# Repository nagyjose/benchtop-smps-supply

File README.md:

# Benchtop Switched-Mode Power Supply (`benchtop-smps-supply`)

> Multi-rail laboratory benchtop power supply providing fixed +12V DC, +5V DC, and dual bipolar adjustable outputs (LM317 / LM337), powered by an isolated offline flyback converter with the Power Integrations TNY267PN.

**Project Status:** `Completed / Hardware Design Ready` | **EDA Tool:** `Autodesk Eagle 9.6.2` | **Category:** `Power Electronics / Hardware`

---

## 1. Overview and Purpose

The **`benchtop-smps-supply`** project is an offline AC/DC power supply engineered for benchtop laboratory instrumentation and electronics prototyping. Powered directly from wide-range AC mains (85–265 V AC, 50/60 Hz), it provides four distinct regulated DC output rails to drive analog circuitry, operational amplifiers, digital microcontrollers, and experimental breadboards:

1. **Fixed +12 V DC Rail:** Regulated via STMicroelectronics L7812 for relay drivers, fans, sensors, and analog stages.
2. **Fixed +5 V DC Rail:** Regulated via STMicroelectronics L7805 for digital logic, microcontrollers (Arduino, STM32), and display modules.
3. **Adjustable Positive Rail (`V+`):** Adjustable from **+1.25 V to ~+15–18 V DC** via Texas Instruments / ST LM317 and a 5 kΩ front-panel potentiometer.
4. **Adjustable Negative Rail (`V-`):** Adjustable from **-1.25 V to ~-15–18 V DC** via Texas Instruments / ST LM337 and a 5 kΩ front-panel potentiometer.

The design combines the high efficiency, compact footprint, and universal mains capability of an offline flyback switching converter with the low-noise, low-ripple characteristics of linear post-regulators.

### Key Features
- **Galvanic Isolation & Safety Compliance:** High-voltage primary and low-voltage secondary circuits are physically separated across a 6.35 mm creepage barrier including a dedicated **2.54 mm isolation milling slot** routed directly under the feedback optocoupler and transformer barrier.
- **EcoSmart® Switching Topology:** Built around the **Power Integrations TNY267PN** TinySwitch-II offline switcher with integrated 700 V power MOSFET, auto-restart protection against output overload/short-circuit, cycle skipping, and thermal shutdown.
- **Multistage Mains Input Protection:** Incorporates a 1A primary melt fuse (`FX1`), a Metal Oxide Varistor surge arrestor (`VAR1`), and an NTC inrush current limiter (`TH1`, 10 Ω).
- **Differential & Common-Mode EMI Filtering:** Features a 2.2 mH common-mode choke (`L1`) and Pi-filter capacitors (`2x 3.3 µF / 400V`) on the rectified high-voltage DC bus.
- **Dual Symmetrical Secondary Output Winding:** Uses a high-performance **Myrra 74080** flyback transformer coupled with **1N5822** Schottky barrier rectifiers and secondary LC smoothing filters (`1000 µF / 470 µF + 10 µH`).
- **Comprehensive Regulator Protection:** Equipped with dedicated reverse-voltage and bypass capacitor discharge protection diodes (`1N4001`) across both LM317 and LM337 linear regulators.
- **Front-Panel Terminal Ready:** Large solder pads for Line, Neutral, Protective Earth (PE), and all output rails for direct wiring to banana jacks, binding posts, or panel meters.

---

## 2. Technical Specifications

| Parameter | Specification | Notes |
| :--- | :--- | :--- |
| **Input Voltage Range** | 85 – 265 V AC (50 / 60 Hz) | Universal worldwide mains |
| **Primary Topology** | Discontinuous Conduction Mode (DCM) Flyback | Low switching losses |
| **Switching Frequency** | ~132 kHz | Controlled by TNY267PN oscillator |
| **Primary Controller IC** | Power Integrations TNY267PN | Integrated 700 V power MOSFET, DIP-8B |
| **Flyback Transformer** | Myrra 74080 | Multi-winding flyback transformer |
| **Feedback Mechanism** | Sharp PC817 Optocoupler + 18V Zener Diode | Galvanically isolated feedback |
| **Fixed Output 1** | **+12.0 V DC** | Linear post-regulated (L7812, TO-220) |
| **Fixed Output 2** | **+5.0 V DC** | Linear post-regulated (L7805, TO-220) |
| **Adjustable Positive Output (`V+`)** | **+1.25 V to ~+15–18 V DC** | Linear regulated (LM317, TO-220) |
| **Adjustable Negative Output (`V-`)** | **-1.25 V to ~-15–18 V DC** | Linear regulated (LM337, TO-220) |
| **Secondary Rectifiers** | 1N5822 (3 A / 40 V Schottky) | Low forward drop, fast recovery |
| **Input Protection** | 1A Fuse + MOV (Varistor) + 10 Ω NTC | Full overcurrent & surge suppression |
| **PCB Form Factor** | Double-sided FR4, 1.6 mm thickness | 94.0 mm × 76.2 mm outline |
| **Isolation Barrier** | 2.54 mm physical milling slot | Creepage compliance between HV and LV |
| **Mounting** | 4× M3 mounting holes (`H1`–`H4`) | Corner chassis mounting |

---

## 3. Architecture & Functional Blocks

The overall converter architecture is structured into six functional stages:

```mermaid
flowchart TD
    subgraph Mains_Input["Mains AC Input Stage"]
        AC["230V AC Mains<br/>(L, N, PE)"] --> PROT["Protection<br/>(1A Fuse + MOV Varistor + 10R NTC)"]
        PROT --> RECT["Full-Bridge Rectifier<br/>(4x 1N4005)"]
        RECT --> DC_BUS["High-Voltage DC Bus (~325V)<br/>(Pi-Filter: 2x 3.3µF / 400V + 2.2mH L1)"]
    end

    subgraph Primary_Flyback["Galvanically Isolated Flyback Converter"]
        DC_BUS --> TR["Flyback Transformer<br/>(Myrra 74080)"]
        DC_BUS --> RCD["RCD Snubber<br/>(1N4005 + 2MΩ / 100kΩ + 2.2nF)"]
        RCD --> TR
        TR <--> TNY["Flyback Controller<br/>(Power Integrations TNY267PN)"]
    end

    subgraph Secondary_Rectification["Secondary Rectification & Filtering"]
        TR --> RECT_SEC["Dual Schottky Rectifiers<br/>(2x 1N5822)"]
        RECT_SEC --> LC_FILT["LC Smoothing Filter<br/>(1000µF / 470µF + 10µH L2, L3)"]
    end

    subgraph Feedback_Loop["Optocoupler Feedback"]
        LC_FILT --> ZD["Zener Reference (18V) + PC817 LED"]
        ZD -.->|Optical Isolation| OPTO_RX["PC817 Phototransistor"]
        OPTO_RX -->|Enable / Skip Cycles| TNY
    end

    subgraph Linear_Regulators["Linear Post-Regulation Stage"]
        LC_FILT --> REG_12V["L7812 (+12V DC Regulated)"]
        LC_FILT --> REG_5V["L7805 (+5V DC Regulated)"]
        LC_FILT --> REG_ADJ_P["LM317 (+1.25V to +18V Adjustable)<br/>with 5k Potentiometer"]
        LC_FILT --> REG_ADJ_N["LM337 (-1.25V to -18V Adjustable)<br/>with 5k Potentiometer"]
    end

    subgraph Output_Terminals["Benchtop Output Terminals"]
        REG_12V --> OUT1["Fixed +12V / GND"]
        REG_5V --> OUT2["Fixed +5V / GND"]
        REG_ADJ_P --> OUT3["V+ Output"]
        REG_ADJ_N --> OUT4["V- Output"]
    end
```

---

## 4. Hardware Schematic & Circuit Diagrams

The complete single-sheet engineering schematic captures the mains input protection, offline flyback converter with TNY267PN, feedback optocoupler with Zener reference, secondary Schottky rectification and LC filtering, fixed post-regulators (+12V and +5V), and adjustable bipolar regulators (LM317 / LM337):

📄 **[Open original schematic in full vector resolution (PDF)](SMPS-BENCH.pdf)**

---

## 5. Bill of Materials (BOM)

### Active Semiconductors & Integrated Circuits
| Designator | Component | Description | Package |
| :--- | :--- | :--- | :--- |
| `IC1` | **TNY267PN** | Power Integrations TinySwitch-II offline switcher | DIP-8B |
| `IC2` | **PC817X4NSZ1B** | Sharp phototransistor optocoupler | DIP-4 |
| `IC3` | **L7812** | STMicroelectronics +12V 1.5A positive linear regulator | TO-220 |
| `IC4` | **L7805** | STMicroelectronics +5V 1.5A positive linear regulator | TO-220 |
| `IC5` | **LM317BT** | Positive adjustable voltage regulator (1.25V to 37V) | TO-220 |
| `IC6` | **LM337SP** | Negative adjustable voltage regulator (-1.25V to -37V) | TO-220 |

### Diodes & Protection
| Designator | Component | Description |
| :--- | :--- | :--- |
| `D1` – `D4` | **1N4005** | Mains bridge rectifier diodes (600 V, 1 A) |
| `D5` | **1N4005** | Primary RCD clamp / snubber diode |
| `D6`, `D8` | **1N5822** | Secondary Schottky barrier rectifier diodes (40 V, 3 A) |
| `D7`, `D10`–`D16` | **1N4001** | Linear regulator reverse-bias and discharge protection |
| `D9` | **18V Zener** | Secondary voltage reference diode |
| `VAR1` | **MOV (HEL-7D681K)** | Metal Oxide Varistor surge suppressor |
| `TH1` | **10R NTC** | Inrush current limiting thermistor |
| `FX1` | **1A Fuse** | Primary mains overcurrent protection fuse |

### Inductive & Passive Components
| Designator | Value / Part | Description |
| :--- | :--- | :--- |
| `TR1` | **Myrra 74080** | Flyback transformer for TinySwitch-II |
| `L1` | **2.2 mH** | High-voltage common-mode / line filter choke |
| `L2`, `L3` | **10 µH** | Secondary post-filter smoothing inductors |
| `C1`, `C2` | **3.3 µF / 400V** | High-voltage electrolytic capacitors (Pi-filter) |
| `C8`, `C9`, `C15`, `C16` | **1000 µF** | Secondary bulk reservoir electrolytic capacitors |
| `C10`, `C17` | **470 µF** | Secondary post-inductor filter capacitors |
| `C18`, `C20` | **10 µF** | Linear regulator output capacitors |
| `C19`, `C21` | **1 µF** | Linear regulator adjust pin bypass capacitors |
| `C3`, `C12`, `C14`, `C22`, `C23` | **100 nF** | Ceramic decoupling capacitors |
| `C4`, `C6`, `C7` | **2.2 nF** | High-voltage ceramic / snubber capacitors |
| `C5` | **1 nF** | Ceramic capacitor |
| `C11`, `C13` | **330 nF** | Ceramic regulator input capacitors |
| `POT1`, `POT2` | **5 kΩ** | Front-panel potentiometers for V+ and V- tuning |
| `R1` | **1.2 kΩ** | Optocoupler current limit resistor |
| `R2` | **2 MΩ** | Primary high-impedance discharge resistor |
| `R3` | **100 kΩ** | Primary snubber damping resistor |
| `R4` | **100 Ω** | Secondary damping resistor |
| `R5` | **680 Ω** | Secondary bias resistor |
| `R6`, `R7` | **240 Ω** | Precision feedback reference resistors for LM317/LM337 |

---

## 6. Directory Structure

```text
.
├── docs/
│   └── images/
│       └── schematic.png        # High-resolution 180 DPI schematic rendering
├── SMPS-BENCH.sch               # Autodesk Eagle schematic
├── SMPS-BENCH.brd               # Autodesk Eagle 2-layer PCB layout
├── SMPS-BENCH.pdf               # Complete schematic and board documentation
├── DRILEGEND.CFG                # Eagle CAM drill table and legend configuration
├── SMPS-BENCH_2025-07-29.zip    # Production CAM output archive (Gerbers, drill, pick & place)
├── SMPS-BENCH_2025-06-29.zip    # Previous CAM release archive
├── .gitignore                   # Ignored Eagle backups (*.b#*, *.s#*, *.epf, *.tmp)
└── README.md                    # Project documentation
```

---

## 7. Manufacturing & Assembly Guidelines

1. **PCB Fabrication:**
   - **Layer Count:** 2-layer FR4.
   - **Board Dimensions:** 94.0 mm × 76.2 mm.
   - **Copper Weight:** 1 oz (35 µm) or 2 oz (70 µm recommended for high secondary currents).
   - **Solder Mask:** Both sides.
   - **Milling / Creepage:** Ensure the milling cutouts under the transformer and optocoupler (layer 20 / milling) are preserved during fabrication.
2. **Heatsinking:**
   - The linear regulators (`IC3`–`IC6`) are designed in TO-220 packages. For currents above 200 mA or large input-to-output voltage deltas, mount small clip-on or chassis-mounted heatsinks.
3. **Safety Notice:**
   - **DANGER - HIGH VOLTAGE:** The primary section operates at rectified mains voltages exceeding **325 V DC**. Always use an isolation transformer during testing and verify that primary bulk capacitors are discharged before handling.
   - Connect the **Protective Earth (PE)** solder pad directly to the metal enclosure chassis.

---

## 8. Related Projects

- [**din-smps**](https://github.com/nagyjose/din-smps): DIN-rail modular power supply based on the same TNY267PN flyback topology with dual fixed rails (+12V & +5V).
- [**F303-voltage-source**](https://github.com/nagyjose/linear-lab-power-supply): Microcontroller-driven (STM32F303) linear laboratory power supply with precision current/voltage feedback.

---

## 9. License & Author

- **Author:** Josef Nagy (`nagyjose`)
- **Status:** Complete Hardware Design

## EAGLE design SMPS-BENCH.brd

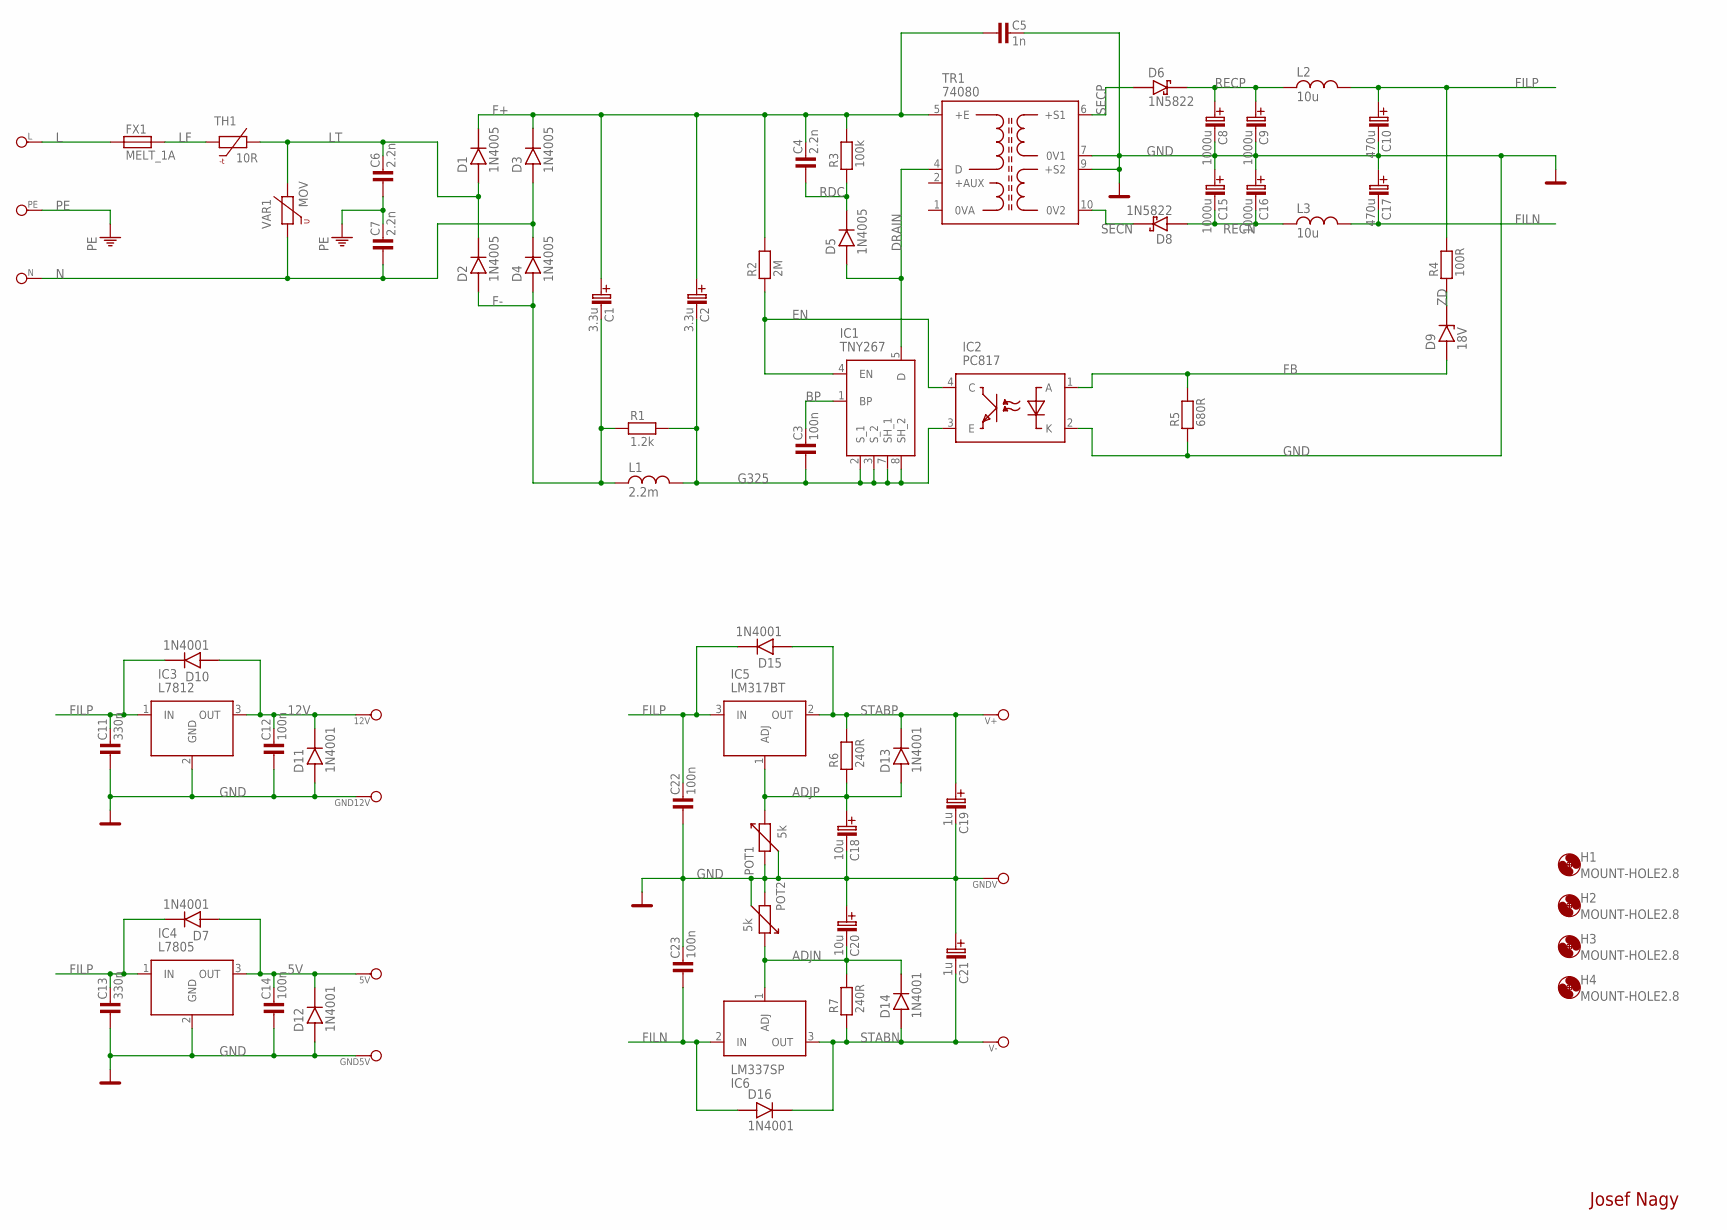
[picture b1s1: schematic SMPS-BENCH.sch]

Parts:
5V, 12V: PAD_1
C1, C2: 3.3u; C-EL_5
C3: 100n; C-10
C4, C6, C7: 2.2n; C-10
C5: 1n; C-10
C8, C9, C15, C16: 1000u; C-EL_5
C10, C17: 470u; C-EL_5
C11, C13: 330n; C-5
C12, C14: 100n; C-2,5
C18, C20: 10u; C-EL_2
C19, C21: 1u; C-EL_2
C22, C23: 100n; C-5
D1, D2, D3, D4, D5: 1N4005; DO41
D6, D8: 1N5822; DO201_V
D7, D10, D11, D12, D13, D14, D15, D16: 1N4001; DO41
D9: 18V; DO35
FX1: MELT_1A; FUSE_MELT
GND5V, GND12V: PAD_1
GNDV: PAD_1
H1, H2, H3, H4: MOUNT-HOLE2.8; 2,8
IC1: TNY267; P-PACKAGE(DIP-8B)_1
IC2: PC817; DIP762W60P254L460H455Q4N
IC3: L7812; TO255P460X1020X2008-3P
IC4: L7805; TO255P460X1020X2008-3P
IC5: LM317BT; TO255P460X1020X2008-3P
IC6: LM337SP; TO255P460X1020X2008-3P
L: PAD_1
L1: 2.2m; L-5
L2, L3: 10u; L-3
N: PAD_1
PE: PAD_1
POT1, POT2: 5k; POT
R1: 1.2k; R-7,5
R2: 2M; R-STOJ2
R3: 100k; R-7,5
R4: 100R; R-7,5
R5: 680R; R-7,5
R6, R7: 240R; R-5
TH1: 10R; THERMISTOR
TR1: 74080
V+: PAD_1
V-: PAD_1
VAR1: MOV; MOV_VARISTOR

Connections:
5V: 5V.1, C14.2, D7.A, D12.K (C), IC4.3 (OUT)
12V: 12V.1, C12.2, D10.A, D11.K (C), IC3.3 (OUT)
ADJN: C20.C- (C_EL-), D14.K (C), IC6.1 (ADJ), POT2.3, R7.2
ADJP: C18.C+ (C_EL+), D13.A, IC5.1 (ADJ), POT1.3, R6.1
BP: C3.2, IC1.1 (BP)
DRAIN: D5.A, IC1.5 (D), TR1.4 (D)
EN: IC1.4 (EN), IC2.4 (C), R2.1
F+: C1.C+ (C_EL+), C2.C+ (C_EL+), C4.2, C5.1, D1.K (C), D3.K (C), R2.2, R3.2, TR1.5 (+E)
F-: C1.C- (C_EL-), D2.A, D4.A, L1.1, R1.1
FB: D9.A, IC2.1 (A), R5.2
FILN: C17.C- (C_EL-), C23.1, D16.A, IC6.2 (IN), L3.2
FILP: C10.C+ (C_EL+), C11.2, C13.2, C22.2, D7.K (C), D10.K (C), D15.K (C), IC3.1 (IN), IC4.1 (IN), IC5.3 (IN), L2.2, R4.2
G325: C2.C- (C_EL-), C3.1, IC1.2 (S_1), IC1.3 (S_2), IC1.7 (SH_1), IC1.8 (SH_2), IC2.3 (E), L1.2, R1.2
GND: C5.2, C8.C- (C_EL-), C9.C- (C_EL-), C10.C- (C_EL-), C11.1, C12.1, C13.1, C14.1, C15.C+ (C_EL+), C16.C+ (C_EL+), C17.C+ (C_EL+), C18.C- (C_EL-), C19.C- (C_EL-), C20.C+ (C_EL+), C21.C+ (C_EL+), C22.1, C23.2, D11.A, D12.A, GND5V.1, GND12V.1, GNDV.1, IC2.2 (K), IC3.2 (GND), IC4.2 (GND), POT1.1, POT1.2, POT2.1, POT2.2, R5.1, TR1.7 (0V1), TR1.9 (+S2)
L: FX1.1, L.1
LF: FX1.2, TH1.1
LT: C6.2, D1.A, D2.K (C), TH1.2, VAR1.2
N: C7.1, D3.A, D4.K (C), N.1, VAR1.1
PE: C6.1, C7.2, PE.1
RDC: C4.1, D5.K (C), R3.1
RECN: C15.C- (C_EL-), C16.C- (C_EL-), D8.A, L3.1
RECP: C8.C+ (C_EL+), C9.C+ (C_EL+), D6.K (C), L2.1
SECN: D8.K (C), TR1.10 (0V2)
SECP: D6.A, TR1.6 (+S1)
STABN: C21.C- (C_EL-), D14.A, D16.K (C), IC6.3 (OUT), R7.1, V-.1
STABP: C19.C+ (C_EL+), D13.K (C), D15.A, IC5.2 (OUT), R6.2, V+.1
ZD: D9.K (C), R4.1

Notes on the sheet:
Josef Nagy

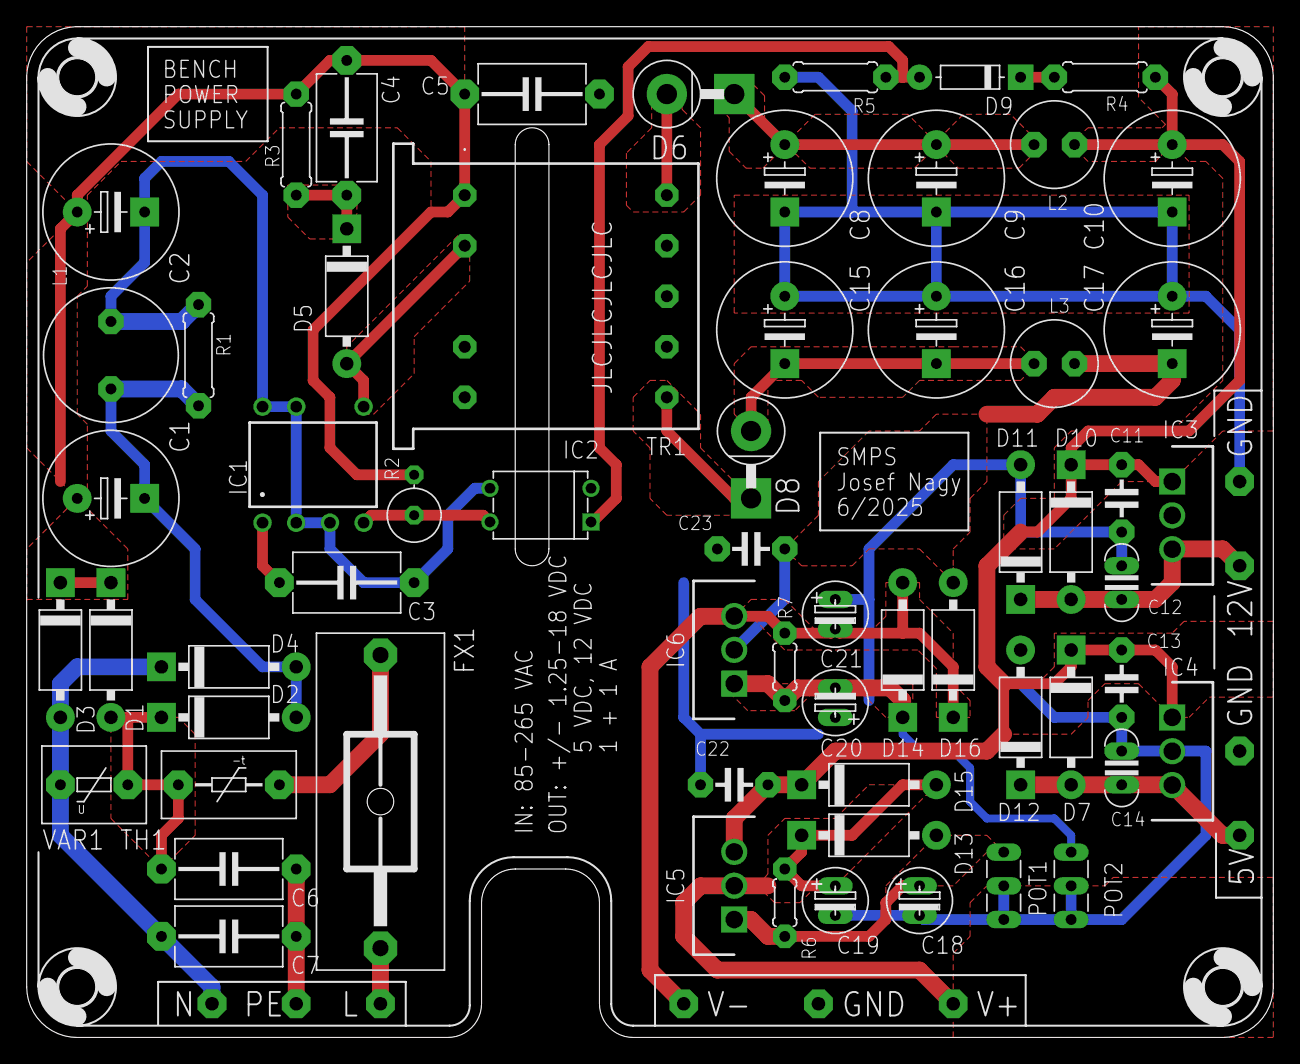
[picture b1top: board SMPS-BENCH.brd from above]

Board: 2 copper layers, 94.0 x 76.2 mm, 75 parts (0 on the bottom side), 27 nets.

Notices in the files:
parts and their libraries:
Copyright (C) PaJa 2001-2014
